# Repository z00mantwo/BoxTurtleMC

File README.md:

# BoxTurtleMC 
BoxTurtle Motor Controller. This is a self sourced DC motor controller for use with [Klipper](https://github.com/ArmoredTurtle/BoxTurtleg) and the  [BoxTurtle](https://klipper3d.org) project. This is not an official [Armored Turtle](https://github.com/ArmoredTurtle) project. Please read the entire file before ordering any parts so you know your options and what is involved. 

The main focus is combining this project with a [BigTreeTech MMB](https://biqu.equipment/products/bigtreetech-mmb). This will enable full BoxTurtle control of the DC motor powered re-spoolers. It also allows a nice upgrade path from a ERCF to the BoxTurtle. It includes additional switch ports to support the "BoxTurtle Lane Controls" mod and additional power connections to support  [Project TurtleScreen](https://github.com/sbtoonz/TurtleScreen). This board will also have the option of controlling up to 8 re-spooler motors so it should be useful in larger custom BoxTurtle setups with more than 4 lanes. 

The board was developed in the free version of [KiCAD](https://www.kicad.org/). So it can be downloaded and modified.

Note there is a mount for the board in the stl folder.

## Making a PCB

Download the latest zip file from the gerber folder. This file can then be submitted to one of the PCB manufactures online like [PCBWay.com](https://www.pcbway.com/), [HQ NextPCB](https://www.nextpcb.com/), [ALLPCB](https://www.allpcb.com/) or [JLCPcb.com](https://jlcpcb.com/). Orders are usually a minimum of 5 PCBs per order and should be around $30 USD for 5 boards including shipping. If this is your first time doing this there are often "first time customer" discounts that can push the cost below $20 including shipping. I suggest shopping around to find the best deal. 

Ideally those who go through the process to make circuit boards will make their extra boards available to others at a minimum cost. The "[Garage Sale](https://discord.com/channels/1229586267671629945/1320411766290907238)" forum in the BoxTurtle Discord is a great place to do this. 

## BOM
All parts are available on Amazon with the exception of the 2 CANBUS plugs.
Those are available at [DigiKey.com](https://DigiKey.com).  

| Item | Quantity | Notes | Links |
| :--- | :---: |:--- | :--- |
PCB | 1 | Required. See "Making a PCB" section | 
Raspberry Pi Pico or Pico 2 | 1 | Required. "W"ireless version is not needed, but will work. | [Amazon](https://www.amazon.com/s?k=Raspberry+Pi+Pico)
1N5817 Diode | 1 | Required. |[Amazon](https://www.amazon.com/s?k=1N5817+Diode)
MP1583EN DC-DC buck converter | 1 | Required. 5V FIXED version highly suggested. Make sure to get version with 8 mounting holes. |  [Amazon](https://www.amazon.com/s?k=MP1583EN+dc-dc+5v+buck+converter)
CJMCU-1051 | 1 | Requied if using CANBUS. CANBUS is the suggested communications method. | [Amazon](https://www.amazon.com/s?k=CJMCU-1051)
DRV8833 DC Motor Driver | 2-4 | One required for each pair of motors. Make sure to get the 12pin 1.5A Dual H Bridge version. | [Amazon](https://www.amazon.com/s?k=DRV8833+DC+Motor+Driver+Controller+Board+3A+Dual+H+Bridge)
Molex Micro-Fit 3.0 43045 | 2 | CANBUS socket. Look at the bottom of the DigiKey page for "Mating Products" if you need the plugs. | [Digikey](https://www.digikey.com/en/products/detail/molex/0430450414/252509)
2.54mm 20 pin female header | 2 |  To socket Pi Pico/Pico 2 | [Amazon](https://www.amazon.com/s?k=2.54mm+Female+Pin+Header)
2.54mm 8 pin female pin header | 1 | For CJMCU-1051.  | [Amazon](https://www.amazon.com/s?k=2.54mm+Female+Pin+Header)
2.54mm 6 pin female pin header | 4 or more | 2 for each DRV8833 module.  | [Amazon](https://www.amazon.com/s?k=2.54mm+Female+Pin+Header)
JST XH 2.54mm 2-pin female sockets | 4 or more | This depends on what parts of the board you will make use of. | [Amazon](https://www.amazon.com/s?k=JST-XH+2.54mm+2pin+female+sockets) 
Through hole 120 Ohm axial resister | 1 | Only needed if CANBUS termination is needed. |  
2pin 2.54mm Pitch Single Row Pin Header | 1,2 | Used for jumper to turn on CANBUS termination. Another one is used for CANH/CANL connection. Both are optional. | [Amazon](https://www.amazon.com/s?k=2.54mm+Pitch+Single+Row+Pin+Header)

If you need to terminate this board use the CAN2 connector for the incoming CANBUS connection. Do not use the CAN1 connection when terminated. 

Note when ordering the Molex Micro-Fit 3.0 connector headers you may also want to order some [Molex Micro-Fit 3.0 plugs](https://www.digikey.com/en/products/detail/molex/0430250408/4481508) along with the appropriate pins [Molex 0430300007](https://www.digikey.com/en/products/detail/molex/0430300007/252479). Since DigiKey allows ordering in specified quantities as low as 1 this may also be a good place to source the needed diode and optional resister.

## Tools Needed
- Basic experience soldering components.
- Soldering iron with fine tip.
- Good solder. Thinner is better.

## Assembling PCB
Solder on the 2 CANBUS plugs and the MP1583EN module. It is recommended that the MP1583EN be soldered to the board and not socketed. If you didn't get a fixed 5V MP1583EN then make sure to set it to 5V. You can do this by connecting the board to a CANBUS connection and adjusting the potentiometer on the MP1583EN while monitoring the output voltage via the 5V connector with a multi meter. Note a fixed 5V MP1583EN is suggested to bypass this step and avoid issues.

Solder in the 1N5817 diode. Note if you are soldering the Pico to the board (not recommended) the diode will need to be installed on the back of the circuit board.

Next solder on the socket connectors as needed. It is recommended to socket the Pico and the DRV8833 modules. The DRV8833 modules are sensitive to static shock. So this makes them easy to replace if needed. 

Solder in the optional CANBUS terminator resister and pin header if needed.

## CANBUS: Flashing Katapult and Klipper

CANBUS needs to already be setup and working on your printer. [Esoterical’s guide](https://canbus.esoterical.online/) is a great resource.

First step is to put Katapult on the Pi Pico. If Katapult isn't already on your Klipper host follow the instructions from the Katapult website to install it on your Klipper host. Instructions are available at [https://github.com/Arksine/katapult](https://github.com/Arksine/katapult). 

Configure katapult as shown below.

Note if you are using a Pi Pico 2 change the "Processor Model" to rp2350.

After configuring and making katapult. Connect your Pi Pico while pressing the boot button on the Pico via USB to your klipper host. It is suggested the Pico is not in the BoxTurtleMC board at this point. 

Then at the hosts command line type lsusb. The Pico should be listed as "Raspberry Pi RP2040 Boot" or "Raspberry Pi RP2350 Boot" if it's a Pico 2. Make a note of the Pico's address. It should be something like "2e8a:000f" as shown below. 

```
~/katapult $ lsusb
Bus 002 Device 002: ID 2109:0817 VIA Labs, Inc. USB3.0 Hub
Bus 002 Device 001: ID 1d6b:0003 Linux Foundation 3.0 root hub
Bus 001 Device 007: ID 0eef:0005 D-WAV Scientific Co., Ltd WS170120
Bus 001 Device 009: ID 1d50:614e OpenMoko, Inc. rp2040
Bus 001 Device 012: ID 2e8a:000f Raspberry Pi RP2350 Boot
Bus 001 Device 006: ID 1d50:606f OpenMoko, Inc. Geschwister Schneider CAN adapter
Bus 001 Device 002: ID 2109:3431 VIA Labs, Inc. Hub
Bus 001 Device 001: ID 1d6b:0002 Linux Foundation 2.0 root hub
```

Now flash the Pico using the following command `sudo make flash device=2e8a:000f` substituting the address of your Pico while in the katapult directory. You should see several messages like below after flashing is complete.

```
~/katapult $ sudo make flash device=2e8a:000f
Flashing out/katapult.uf2
Loaded UF2 image with 29 pages
Found rp2040 device on USB bus 1 address 11
Flashing...
Resetting interface
Locking
Exiting XIP mode
Erasing
Flashing
Rebooting device
```

Put you Pico in the BoxTurtleMC board and connect the board to your CANBUS cable. Make sure to power everything off before doing that and then bring everything back up.

Check if the Pico is detected on the CANBUS with the command `~/klipper/scripts/canbus_query.py can0`. Output should look something like:

```
~/klipper $ ~/klippy-env/bin/python ~/klipper/scripts/canbus_query.py can0
Found canbus_uuid=05a32df28477, Application: Klipper
Total 1 uuids found
```

If the Pico isn't found then something went wrong in the process of flashing or something is wrong with your CANBUS cabling or setup.

Record the UUID given for the Pico. You will need this to flash klipper and to configure klipper.

Reconnect to the command line on your klipper host. Next change to the klipper directory. There run the command `make menuconfig` and change the settings as shown below.

Note if you are using a Pi Pico 2 change the "Processor Model" to rp2350.

Make klipper then flash it to the Pico with the command below. Substitute the uuid (XXXXXXXXXXXX) with your Pico's uuid you recorded above.

```
cd ~/katapult/scripts && python3 flashtool.py -i can0 -f ~/klipper/out/klipper.bin -u XXXXXXXXXXXX
```

If all is well the Pico will reboot and there should be a green light on the Pi Pico and a red light on each DRV8833. If the Pico light does not come on power off and back on. If it still does not come on something went wrong along the way. 

## Klipper configuration

Copy the `MC_1.cfg` in the klipper folder to your klipper configurations folder. 

Then add

```
[include MC_1.cfg]
```

to your `printer.cfg`. Make sure this is before you load the [AFC-Klipper-Add-On](https://github.com/ArmoredTurtle/AFC-Klipper-Add-On/tree/main) cfg files. 

Note that with the DRV8833 modules use one line controls the SLEEP/ENABLE option for 2 motors. So rather than a MOT1_EN alias the BoxTurtleMC has a MOT12_EN alias that is the ENABLE function for both motor 1 and motor 2.

This then requires setting a `[duplicate_pin_override]` section in your klipper configuration. See the example near the end of the `MC_1.cfg` file for an example. Note that if you don't have a `[duplicate_pin_override]` section in your current configuration you can uncomment the section in the `MC_1.cfg` file.

If you are combining the BoxTurtleMC with BTT MMB you will need to edit the AFC/mcu/MMB_1.0.cfg or MMB_1.1.cfg and remove or comment out the MOT lines by placing a # in front of each line.

```
	#MOT1_RWD=PA0	, 
	#MOT2_RWD=PA1	, 
	#MOT3_RWD=PB10	, 
	#MOT4_RWD=PB2	,
```

Then you need to change the "afc_motor" entries in your `AFC/AFC_Turtle_1.cfg` file for each lane that you want the re-spooler motors controlled by the BoxTurtleMC. For example change

```
afc_motor_rwd: Turtle_1:MOT1_RWD
afc_motor_fwd: Turtle_1:MOT1_FWD
afc_motor_enb: Turtle_1:MOT1_EN
```

to

```
afc_motor_rwd: MC_1:MOT1_RWD
afc_motor_fwd: MC_1:MOT1_FWD
afc_motor_enb: MC_1:MOT12_EN
```

You will need to do this for each lane that you want the BoxTurtleMC to control the DC motor in the re-spooler. 

Use the [AFC Klipper Add-on](https://github.com/ArmoredTurtle/AFC-Klipper-Add-On/)'s "TEST lane=lane1" to check each motor control is setup properly. 

## Options
- You can use a JST XH 2.54mm 2-pin female socket for the CANH/CANL rather than a 2 pin header if you want.
 
- Only purchasing the components you need. All locations on the board do not need to be populated. You can choose and select the ones you want to populate based on your intended usage. Below is a board setup to only use motors 1-4.

- A question was asked about using this board with a cheap Ender 3 SKR board. Most of the SKR boards only have 4 switches. X, Y, Z limit switches and a filament detection switch. When combined with this board's 6 switches that would only be 10 switches and 11 are needed for a 4 lane BoxTurtle. The DRV3 socket can be used to add a 7th switch as shown below. Make sure to orient the socket as shown. This would make the 7th switch GPIO12. NOTE THIS HAS NOT BEEN TESTED, but should work.

- Using USB rather than CANBUS. This board can be used by klipper through the USB connector on the Pi Pico. The CJMCU-1051 could then be excluded, but the board would still need external 24V power for the DRV8833s. This can be connected via one of the CANBUS connectors. This will require install klipper (no katapult) as configured below. Only recommended for experienced klipper users. 

Note if you are using a Pi Pico 2 change the "Processor Model" to rp2350.

## Version 1.1.2 boards (Current Release)
This is a minor upgrade over 1.1 boards. It added 2 additional switches when DRV4 is not populated and an additional 9th switch when DRV3 is also not populated. This is primarily to support using this board with MCUs that have a limited number of switch connections. To get to the required 11 switches needed for a base model, 4 lane, BoxTurtle.

## Version 1.1 boards
Release 1.1 boards only included 6 switches. Two of which only worked if DRV4 is left empty. This was the first version released. 

## Early release 1.0 boards
Note the 1.0 board does have a known issue. The CANL and CANH pins are reversed. Still works, but where katapult and klipper want to use pins 4 and 5 as defaults you have to switch them to 5 then 4. Version 1.1 board fixes this. See the screenshots in the "Flashing Katapult and Klipper" section above.

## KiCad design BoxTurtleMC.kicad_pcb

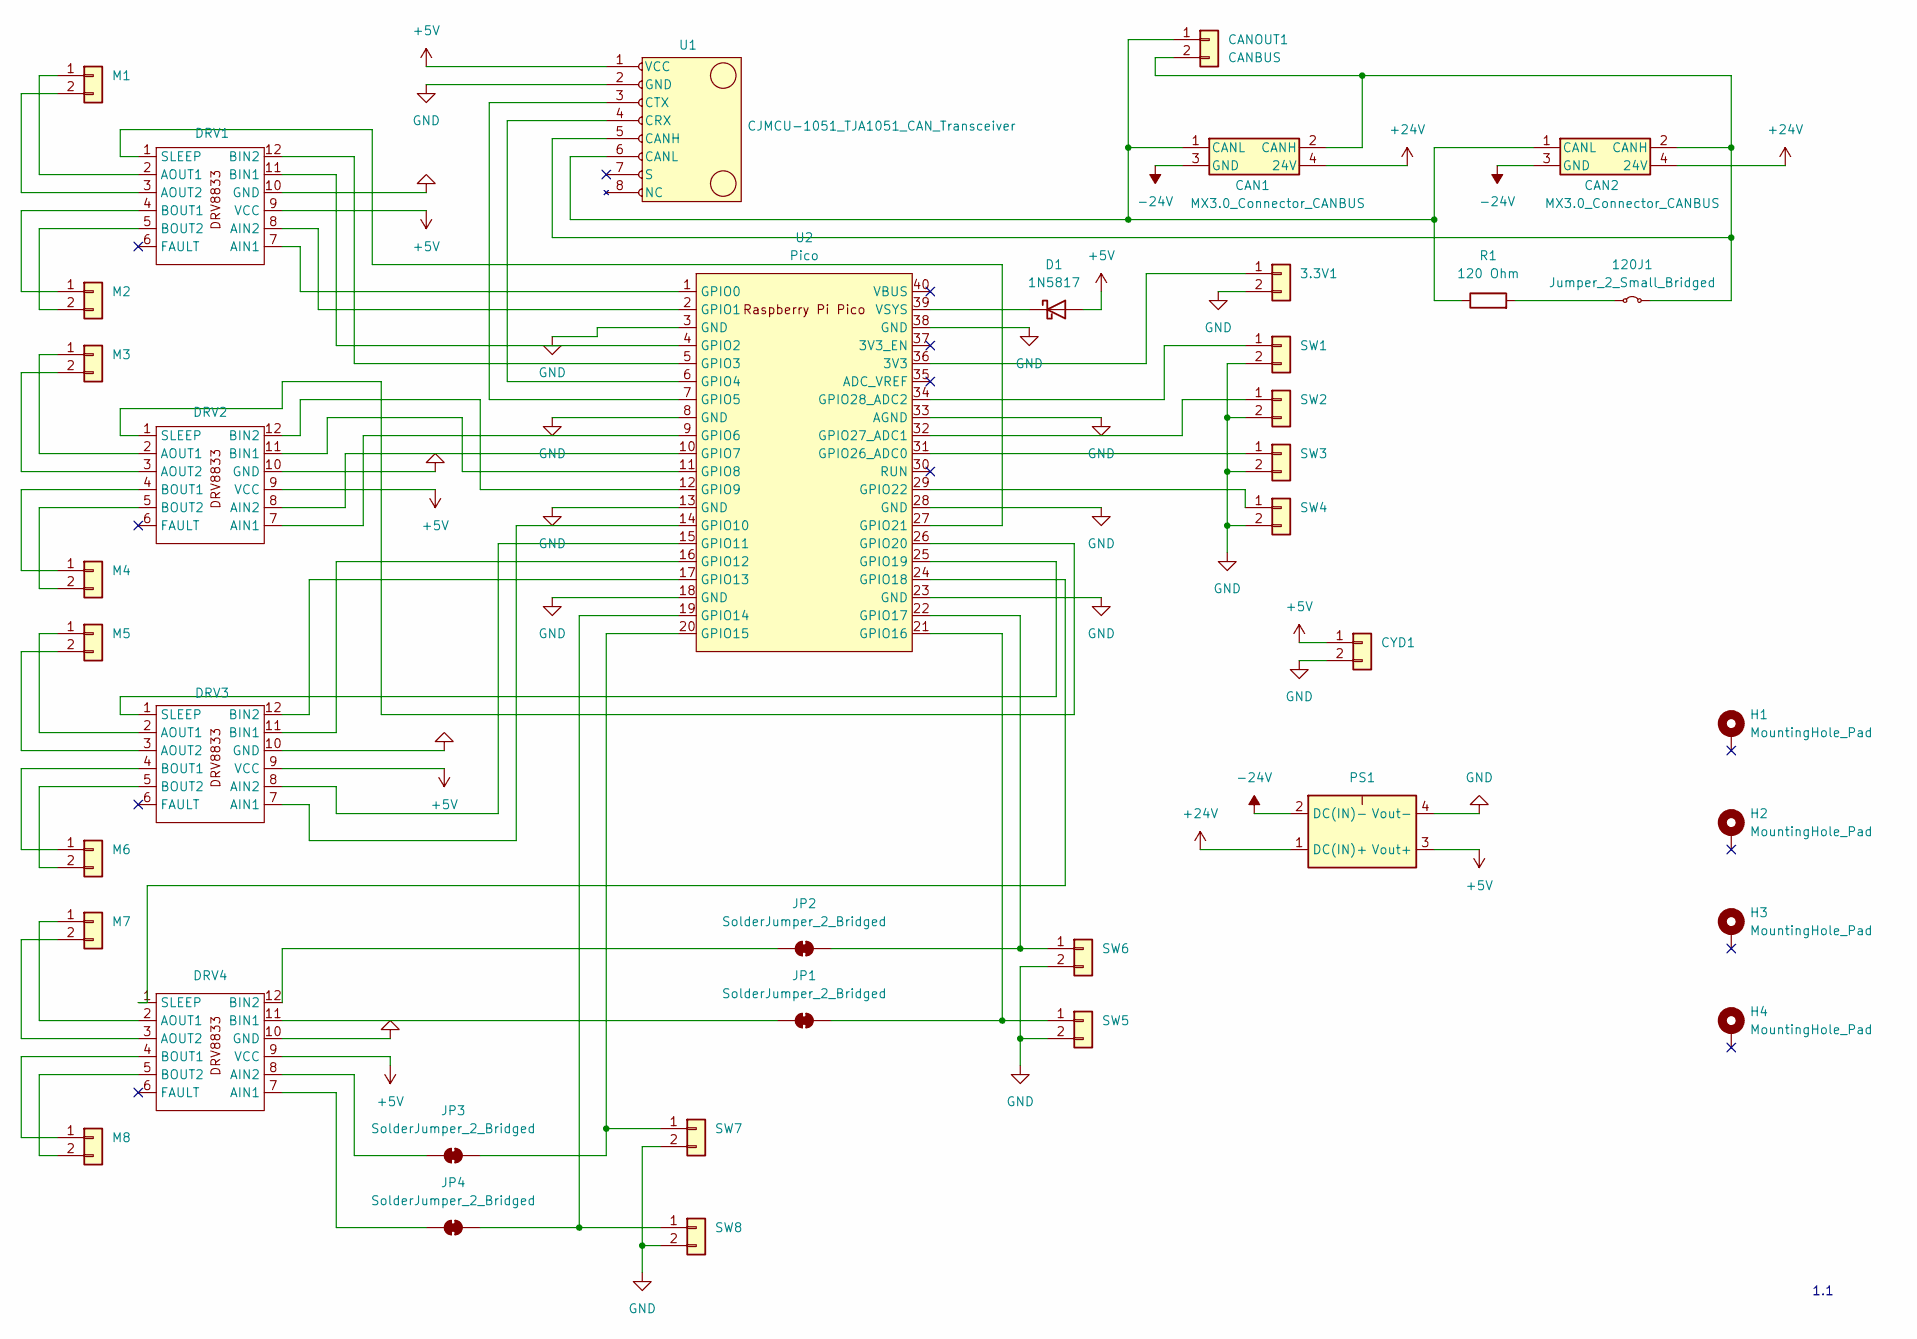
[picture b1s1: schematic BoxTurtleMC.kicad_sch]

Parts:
3.3V1: 1; JST_XH_B2B-XH-A_1x02_P2.50mm_Vertical
120J1: Jumper_2_Small_Bridged; PinHeader_1x02_P2.54mm_Vertical
CAN1, CAN2: MX3.0_Connector_CANBUS; MX3.0 Connector CANBUS
CANOUT1: CANBUS; PinHeader_1x02_P2.54mm_Vertical
CYD1: 1; JST_XH_B2B-XH-A_1x02_P2.50mm_Vertical
D1: 1N5817; D_DO-41_SOD81_P10.16mm_Horizontal
DRV1, DRV2, DRV3, DRV4: DRV8833_Module
H1, H2, H3, H4: MountingHole_Pad; MountingHole_3.2mm_M3_Pad_TopBottom
JP1, JP2, JP3, JP4: SolderJumper_2_Bridged; SolderJumper-2_P1.3mm_Bridged_RoundedPad1.0x1.5mm
M1, M2, M3, M4, M5, M6, M7, M8: Conn_01x02 Pin1+ Pin2-; JST_XH_B2B-XH-A_1x02_P2.50mm_Vertical
PS1: MP1583_Module; MP1584_Module
R1: 120 Ohm; R_Axial_DIN0207_L6.3mm_D2.5mm_P10.16mm_Horizontal
SW1, SW2, SW3, SW4, SW5, SW6, SW7, SW8: Conn_01x02 Pin1+ Pin2-; JST_XH_B2B-XH-A_1x02_P2.50mm_Vertical
U1: CJMCU-1051_TJA1051_CAN_Transceiver
U2: Pico; RaspberryPi_Pico_Common_THT

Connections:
+5V: CYD1.1, D1.2 (A), DRV1.9 (VCC), DRV2.9 (VCC), DRV3.9 (VCC), DRV4.9 (VCC), PS1.3 (Vout+), U1.1 (VCC)
+24V: CAN1.4 (24V), CAN2.4 (24V), PS1.1 (DC(IN)+)
-24V: CAN1.3 (GND), CAN2.3 (GND), PS1.2 (DC(IN)-)
GND: 3.3V1.2, CYD1.2, DRV1.10 (GND), DRV2.10 (GND), DRV3.10 (GND), DRV4.10 (GND), PS1.4 (Vout-), SW1.2, SW2.2, SW3.2, SW4.2, SW5.2, SW6.2, SW7.2, SW8.2, U1.2 (GND), U2.3 (GND), U2.8 (GND), U2.13 (GND), U2.18 (GND), U2.23 (GND), U2.28 (GND), U2.33 (AGND), U2.38 (GND)
unnamed: 3.3V1.1, U2.36 (3V3)
unnamed: 120J1.1 (A), R1.2
unnamed: 120J1.2 (B), CAN1.2 (CANH), CAN2.2 (CANH), CANOUT1.2, U1.5 (CANH)
unnamed: CAN1.1 (CANL), CAN2.1 (CANL), CANOUT1.1, R1.1, U1.6 (CANL)
unnamed: D1.1 (K), U2.39 (VSYS)
unnamed: DRV1.7 (AIN1), U2.1 (GPIO0)
unnamed: DRV1.8 (AIN2), U2.2 (GPIO1)
unnamed: DRV1.2 (AOUT1), M1.1
unnamed: DRV1.3 (AOUT2), M1.2
unnamed: DRV1.11 (BIN1), U2.4 (GPIO2)
unnamed: DRV1.12 (BIN2), U2.5 (GPIO3)
unnamed: DRV1.4 (BOUT1), M2.1
unnamed: DRV1.5 (BOUT2), M2.2
unnamed: DRV1.1 (SLEEP), U2.27 (GPIO21)
unnamed: DRV2.7 (AIN1), U2.9 (GPIO6)
unnamed: DRV2.8 (AIN2), U2.10 (GPIO7)
unnamed: DRV2.2 (AOUT1), M3.1
unnamed: DRV2.3 (AOUT2), M3.2
unnamed: DRV2.11 (BIN1), U2.11 (GPIO8)
unnamed: DRV2.12 (BIN2), U2.12 (GPIO9)
unnamed: DRV2.4 (BOUT1), M4.1
unnamed: DRV2.5 (BOUT2), M4.2
unnamed: DRV2.1 (SLEEP), U2.26 (GPIO20)
unnamed: DRV3.7 (AIN1), U2.14 (GPIO10)
unnamed: DRV3.8 (AIN2), U2.15 (GPIO11)
unnamed: DRV3.2 (AOUT1), M5.1
unnamed: DRV3.3 (AOUT2), M5.2
unnamed: DRV3.11 (BIN1), U2.16 (GPIO12)
unnamed: DRV3.12 (BIN2), U2.17 (GPIO13)
unnamed: DRV3.4 (BOUT1), M6.1
unnamed: DRV3.5 (BOUT2), M6.2
unnamed: DRV3.1 (SLEEP), U2.25 (GPIO19)
unnamed: DRV4.7 (AIN1), JP4.1 (A)
unnamed: DRV4.8 (AIN2), JP3.1 (A)
unnamed: DRV4.2 (AOUT1), M7.1
unnamed: DRV4.3 (AOUT2), M7.2
unnamed: DRV4.11 (BIN1), JP1.1 (A)
unnamed: DRV4.12 (BIN2), JP2.1 (A)
unnamed: DRV4.4 (BOUT1), M8.1
unnamed: DRV4.5 (BOUT2), M8.2
unnamed: DRV4.1 (SLEEP), U2.24 (GPIO18)
unnamed: JP1.2 (B), SW5.1, U2.21 (GPIO16)
unnamed: JP2.2 (B), SW6.1, U2.22 (GPIO17)
unnamed: JP3.2 (B), SW7.1, U2.20 (GPIO15)
unnamed: JP4.2 (B), SW8.1, U2.19 (GPIO14)
unnamed: SW1.1, U2.34 (GPIO28_ADC2)
unnamed: SW2.1, U2.32 (GPIO27_ADC1)
unnamed: SW3.1, U2.31 (GPIO26_ADC0)
unnamed: SW4.1, U2.29 (GPIO22)
unnamed: U1.4 (CRX), U2.6 (GPIO4)
unnamed: U1.3 (CTX), U2.7 (GPIO5)

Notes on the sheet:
1.1

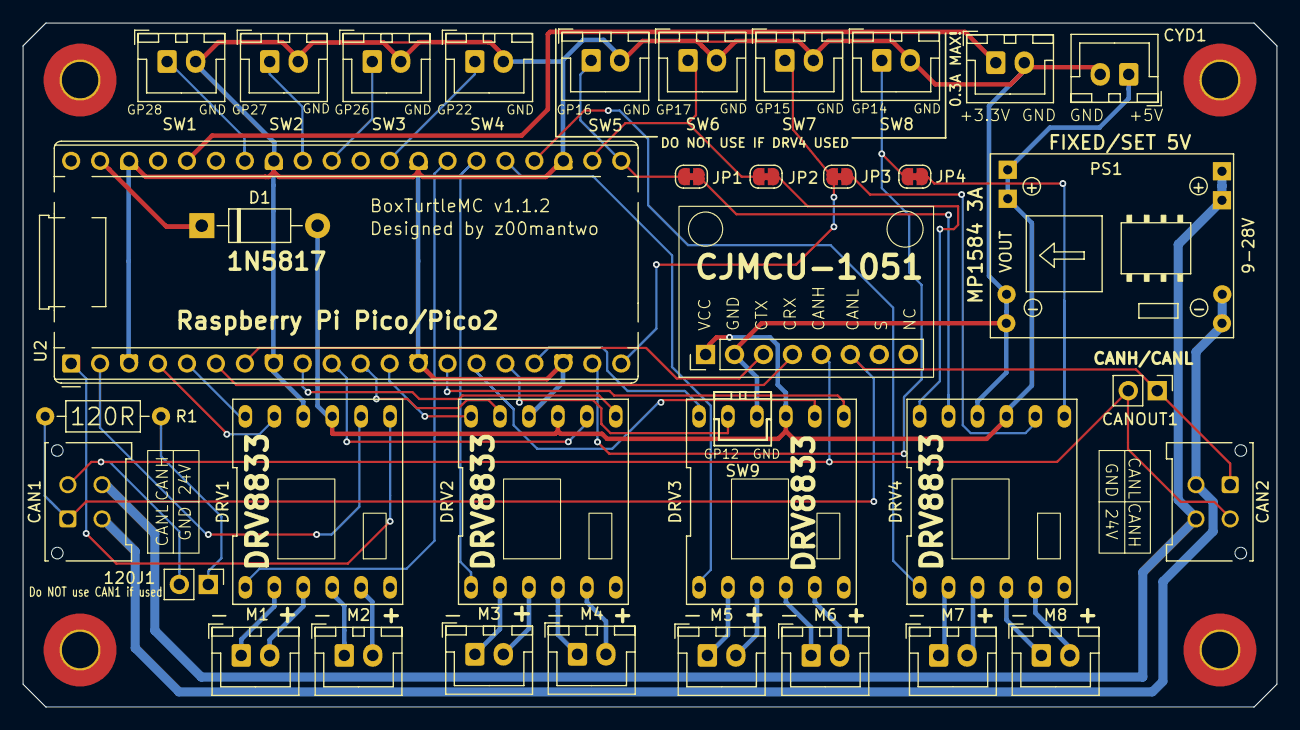
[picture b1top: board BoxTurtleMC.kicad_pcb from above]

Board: 2 copper layers, 110.0 x 60.0 mm, 39 parts (0 on the bottom side), 55 nets.

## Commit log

2025-03-23 First update test
2025-03-23 Additional updates
2025-03-23 Test2
2025-03-23 Doc updates
2025-03-23 images update
2025-03-25 Added .gitignore
2025-04-03 Fix pin miss coding for motor 7 8
2025-04-03 Minor update to README.md
2025-04-03 Fixed some labels in schematic
2025-04-03 Fix file list
2025-04-04 Additional updates to README
2025-04-07 Added notes about using with Ender 3 SKR board.
2025-04-07 Added notes about using with Ender 3 SKR board with pic
2025-04-07 Updated klipper config for SW5, SW6 and SW7.
2025-04-08 Added setup for USB connection
2025-04-09 Minor change to README.md
2025-07-11 README fixes
